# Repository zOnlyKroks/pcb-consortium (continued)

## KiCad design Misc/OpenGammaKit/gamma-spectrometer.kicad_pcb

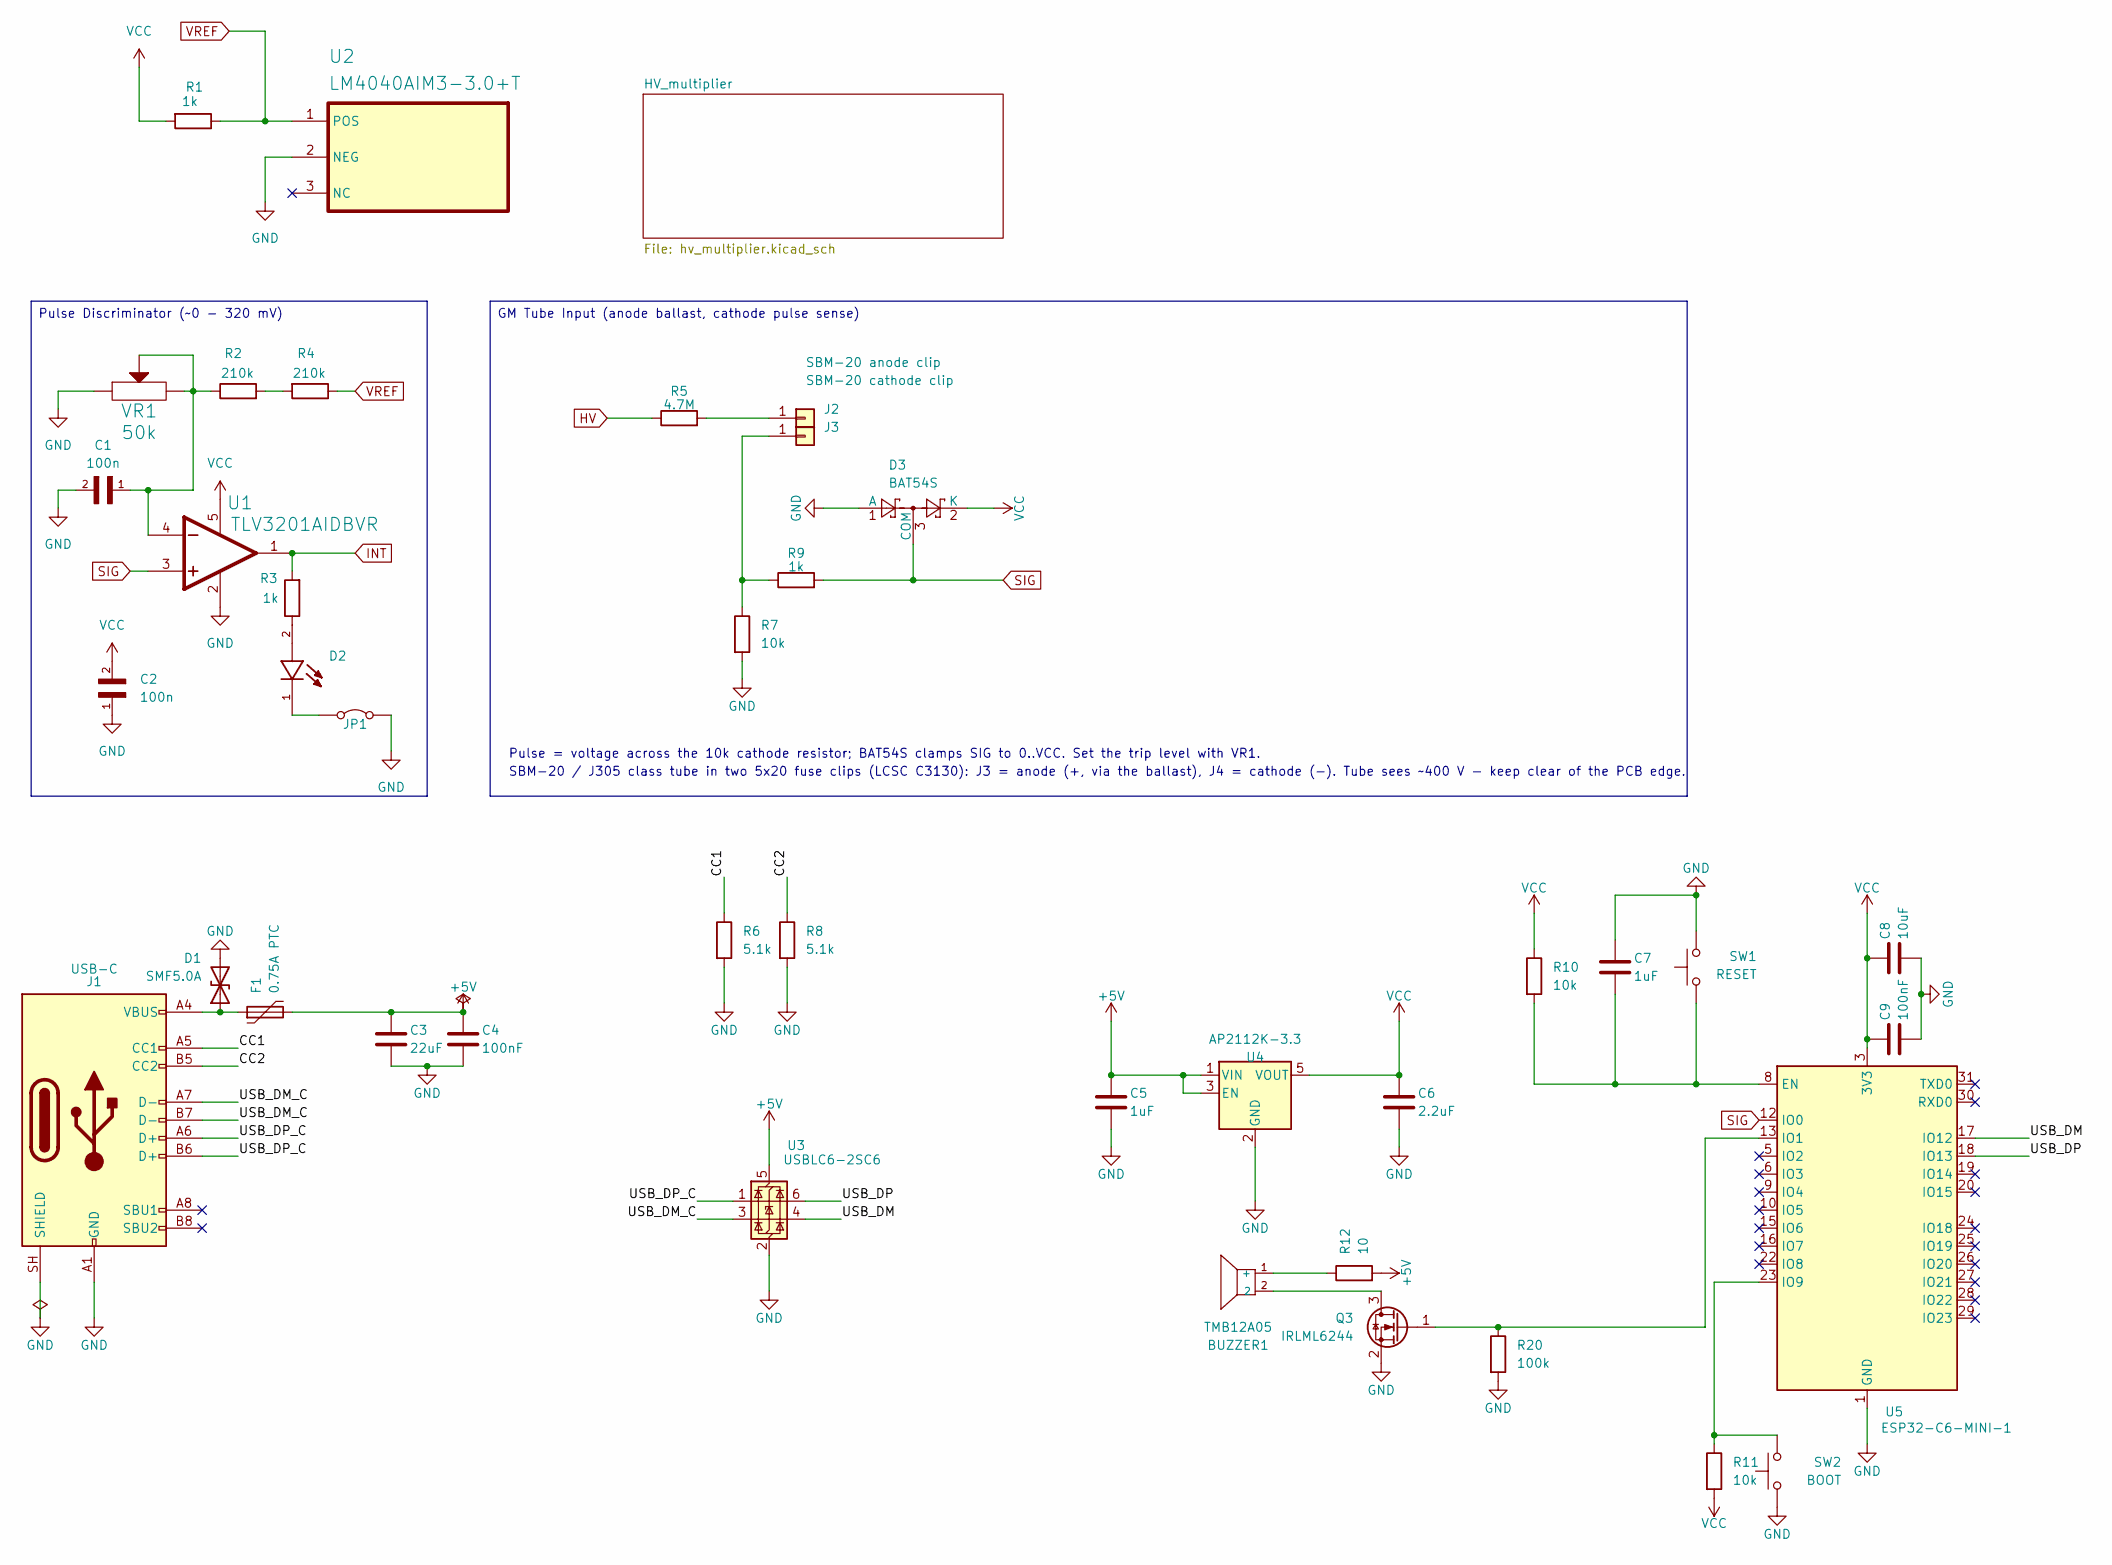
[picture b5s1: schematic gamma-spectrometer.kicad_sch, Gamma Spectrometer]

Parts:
BUZZER1: TMB12A05; C96093_BUZ-TH_BD12_0-P7_60-D0_6-FD; LCSC C96093
C1, C2: 100n; C_0603_1608Metric; PARTREV NA
C3: 22uF; C_1206_3216Metric
C4, C9: 100nF; C_0603_1608Metric
C5, C7: 1uF; C_0603_1608Metric
C6: 2.2uF; C_0603_1608Metric
C8: 10uF; C_0805_2012Metric
D1: SMF5.0A; D_SOD-123; LCSC C193402
D2: LTST-C190KGKT; LED_0603_1608Metric; LCSC C125094
D3: BAT54S; SOT-23; LCSC C458984
F1: 0.75A PTC; Fuse_1206_3216Metric; LCSC C47002356
J1: USB-C; USB_C_Receptacle_HRO_TYPE-C-31-M-12; LCSC C165948
J2: SBM-20 anode clip; FUSE-TH_5X20RHOSFUSECLIP-SEAT; LCSC C3130
J3: SBM-20 cathode clip; FUSE-TH_5X20RHOSFUSECLIP-SEAT; LCSC C3130
JP1: SolderJumper-2_P1.3mm_Open_TrianglePad1.0x1.5mm
Q3: IRLML6244; SOT-23; LCSC C143946
R1, R3, R9: 1k; R_0603_1608Metric
R2, R4: 210k; R_0603_1608Metric
R5: 4.7M; R_0603_1608Metric
R6, R8: 5.1k; R_0603_1608Metric
R7, R10, R11: 10k; R_0603_1608Metric
R12: 10; R_0603_1608Metric
R20: 100k; R_0603_1608Metric
SW1: RESET; SW_TS-1187A-B-A-B_2pin; LCSC C318884
SW2: BOOT; SW_TS-1187A-B-A-B_2pin; LCSC C318884
U1: TLV3201AIDBVR; SOT-23-5; LCSC C105188
U2: LM4040AIM3-3.0+T; SOT-23; LCSC C143326
U3: USBLC6-2SC6; SOT-23-6; LCSC C7519
U4: AP2112K-3.3; SOT-23-5; MPN AP2112K-3.3TRG1; LCSC C51118
U5: ESP32-C6-MINI-1; MPN ESP32-C6-MINI-1-N4; LCSC C5736265
VR1: 50k; Potentiometer_Bourns_3266W_Vertical

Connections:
+5V: C3.1, C4.1, C5.1, F1.2, R12.2, U3.5 (VBUS), U4.1 (VIN), U4.3 (EN); also elsewhere on the board
/CC1: J1.A5 (CC1), R6.1
/CC2: J1.B5 (CC2), R8.1
/USB_DM: U3.4 (I/O2), U5.17 (IO12)
/USB_DM_C: J1.A7 (D-), J1.B7 (D-), U3.3 (I/O2)
/USB_DP: U3.6 (I/O1), U5.18 (IO13)
/USB_DP_C: J1.A6 (D+), J1.B6 (D+), U3.1 (I/O1)
GND: C1.2, C2.1, C3.2, C4.2, C5.2, C6.2, C7.1, C8.2, C9.2, D1.2 (A2), D3.1 (A), J1.A1 (GND), J1.A12 (GND), J1.B1 (GND), J1.B12 (GND), J1.SH (SHIELD), JP1.2 (B), Q3.2 (S), R6.2, R7.2, R8.2, R20.2, SW1.2, SW2.1, U1.2 (GND), U2.2 (NEG), U3.2 (GND), U4.2 (GND), U5.1 (GND), U5.2 (GND), U5.11 (GND), U5.14 (GND), U5.36 (GND), U5.37 (GND), U5.38 (GND), U5.39 (GND), U5.40 (GND), U5.41 (GND), U5.42 (GND), U5.43 (GND), U5.44 (GND), U5.45 (GND), U5.46 (GND), U5.47 (GND), U5.48 (GND), U5.49 (GND), U5.50 (GND), U5.51 (GND), U5.52 (GND), U5.53 (GND), VR1.1 (CCW); also elsewhere on the board
HV: R5.1; also elsewhere on the board
INT: R3.2, U1.1 (OUT)
unnamed: BUZZER1.1 (+), R12.1
unnamed: D1.1 (A1), F1.1, J1.A4 (VBUS), J1.A9 (VBUS), J1.B4 (VBUS), J1.B9 (VBUS)
unnamed: D2.2, R3.1
unnamed: J2.1 (Pin_1_1), R5.2
unnamed: J3.1 (Pin_1_1), R7.1, R9.1
unnamed: D2.1, JP1.1 (A)
unnamed: BUZZER1.2, Q3.3 (D)
unnamed: Q3.1 (G), R20.1, U5.13 (IO1)
unnamed: R2.2, R4.2
unnamed: C1.1, R2.1, U1.4 (IN-), VR1.2 (WIPER), VR1.3 (CW)
unnamed: C7.2, R10.2, SW1.1, U5.8 (EN)
unnamed: R11.1, SW2.2, U5.23 (IO9)
SIG: D3.3 (COM), R9.2, U1.3 (IN+), U5.12 (IO0)
VCC: C2.2, C6.1, C8.1, C9.1, D3.2 (K), R1.2, R10.1, R11.2, U1.5 (VCC), U4.5 (VOUT), U5.3 (3V3); also elsewhere on the board
VREF: R1.1, R4.1, U2.1 (POS); also elsewhere on the board

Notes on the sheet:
SBM-20 / J305 class tube in two 5x20 fuse clips (LCSC C3130): J3 = anode (+, via the ballast), J4 = cathode (-). Tube sees ~400 V - keep clear of the PCB edge.
Pulse = voltage across the 10k cathode resistor; BAT54S clamps SIG to 0..VCC. Set the trip level with VR1.
Pulse Discriminator (~0 - 320 mV)
GM Tube Input (anode ballast, cathode pulse sense)

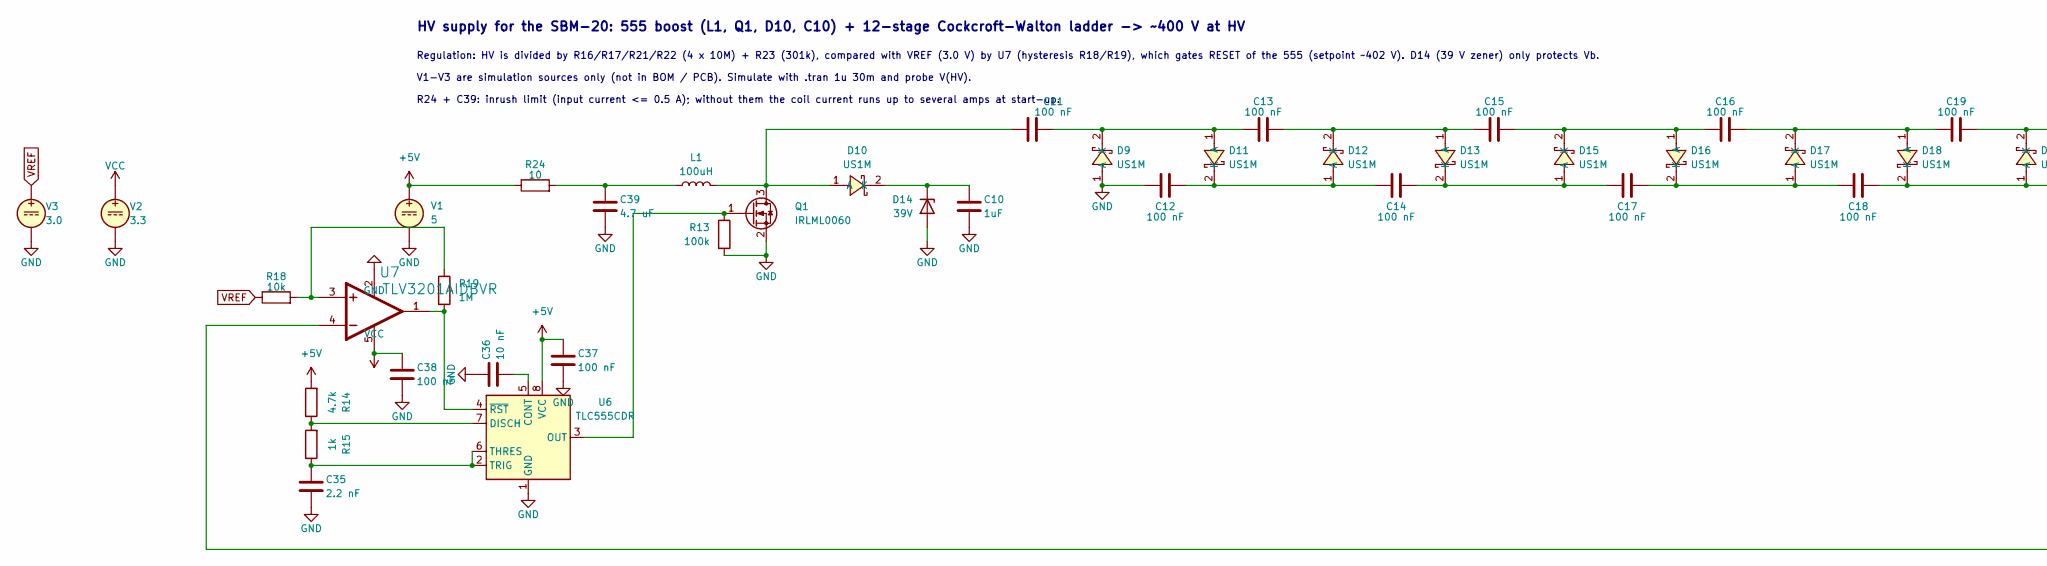
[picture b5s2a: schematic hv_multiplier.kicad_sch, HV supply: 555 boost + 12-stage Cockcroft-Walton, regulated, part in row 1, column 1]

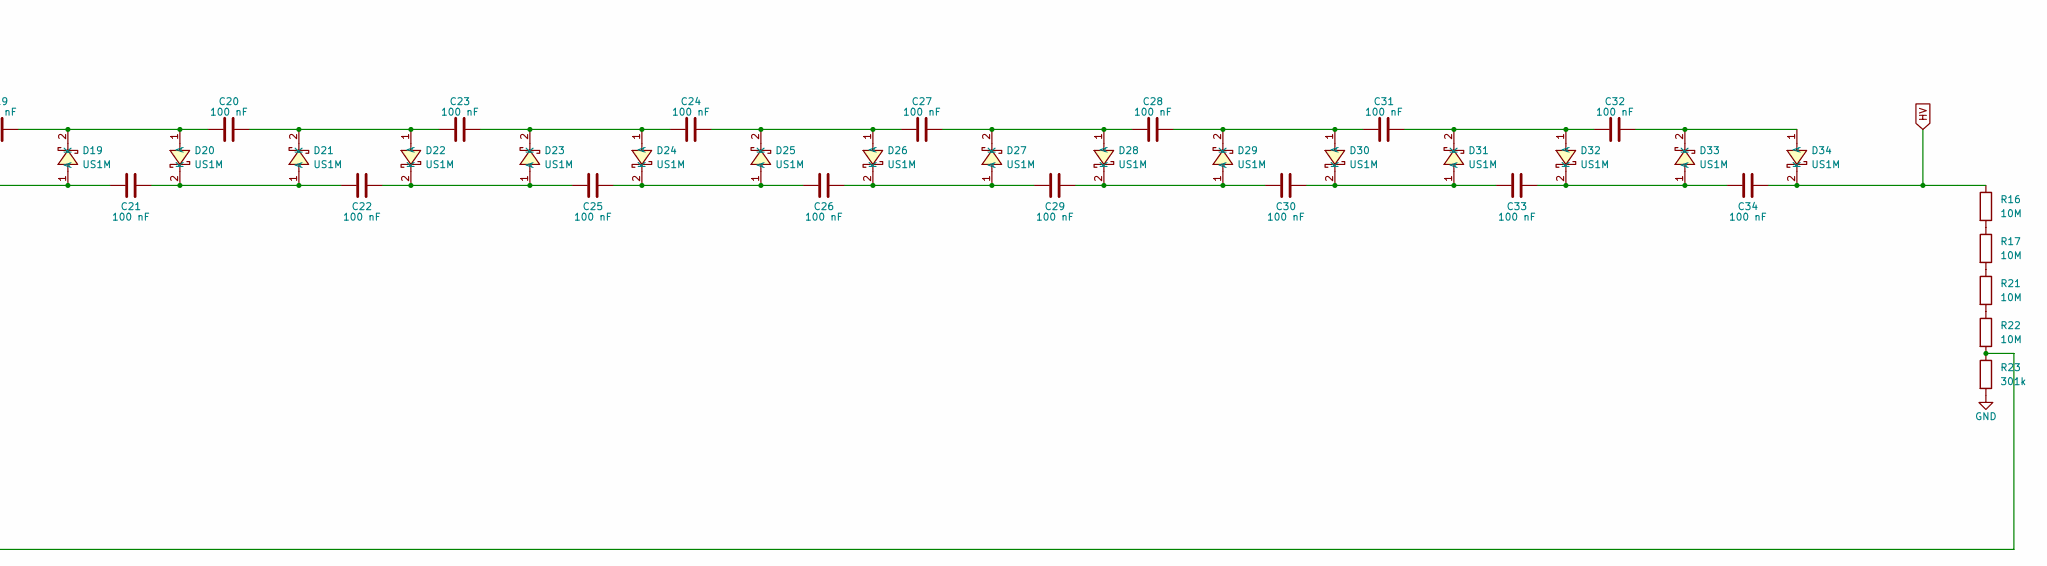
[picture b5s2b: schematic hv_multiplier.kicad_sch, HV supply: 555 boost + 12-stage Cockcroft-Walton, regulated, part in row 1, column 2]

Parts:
C10: 1uF; C_1206_3216Metric; LCSC C13832
C11, C12, C13, C14, C15, C16, C17, C18, C19, C20, C21, C22, C23, C24, C25, C26, C27, C28, C29, C30, C31, C32, C33, C34: 100 nF; C_0805_2012Metric; LCSC C28233
C35: 2.2 nF; C_0603_1608Metric
C36: 10 nF; C_0603_1608Metric
C37, C38: 100 nF; C_0603_1608Metric
C39: 4.7 uF; C_0805_2012Metric; LCSC C1746
D9, D10, D11, D12, D13, D15, D16, D17, D18, D19, D20, D21, D22, D23, D24, D25, D26, D27, D28, D29, D30, D31, D32, D33, D34: US1M; C7420317_SMA_L4.3-W2.6-LS5.0-FD; LCSC C7420317
D14: 39V; D_SOD-123; LCSC C353532
L1: 100uH; C280633_IND-SMD_L10.5-W10.5; LCSC C280633
Q1: IRLML0060; SOT-23; LCSC C67274
R13: 100k; R_0603_1608Metric
R14: 4.7k; R_0603_1608Metric
R15: 1k; R_0603_1608Metric
R16, R17, R21, R22: 10M; R_0805_2012Metric; LCSC C325949
R18: 10k; R_0603_1608Metric
R19: 1M; R_0603_1608Metric
R23: 301k; R_0603_1608Metric
R24: 10; R_2512_6332Metric; LCSC C171290
U6: TLC555CDR; SOIC-8_3.9x4.9mm_P1.27mm; LCSC C6986
U7: TLV3201AIDBVR; SOT-23-5; LCSC C105188
V1: 5
V2: 3.3
V3: 3.0

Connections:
+5V: C37.1, R14.2, R24.1, U6.8 (VCC), V1.1; also elsewhere on the board
GND: C10.2, C12.1, C35.2, C36.1, C37.2, C38.2, C39.2, D9.1 (A), D14.2 (A), Q1.2 (S), R13.2, R23.2, U6.1 (GND), U7.2 (GND), V1.2, V2.2, V3.2; also elsewhere on the board
HV: C34.2, D34.2 (K), R16.1; also elsewhere on the board
unnamed: C39.1, L1.1, R24.2
unnamed: C11.1, D10.1 (A), L1.2, Q1.3 (D)
unnamed: C10.1, D10.2 (K), D14.1 (K)
unnamed: C11.2, C13.1, D9.2 (K), D11.1 (A)
unnamed: C12.2, C14.1, D11.2 (K), D12.1 (A)
unnamed: C13.2, C15.1, D12.2 (K), D13.1 (A)
unnamed: C14.2, C17.1, D13.2 (K), D15.1 (A)
unnamed: C15.2, C16.1, D15.2 (K), D16.1 (A)
unnamed: C17.2, C18.1, D16.2 (K), D17.1 (A)
unnamed: C16.2, C19.1, D17.2 (K), D18.1 (A)
unnamed: C18.2, C21.1, D18.2 (K), D19.1 (A)
unnamed: C19.2, C20.1, D19.2 (K), D20.1 (A)
unnamed: C21.2, C22.1, D20.2 (K), D21.1 (A)
unnamed: C20.2, C23.1, D21.2 (K), D22.1 (A)
unnamed: C22.2, C25.1, D22.2 (K), D23.1 (A)
unnamed: C23.2, C24.1, D23.2 (K), D24.1 (A)
unnamed: C25.2, C26.1, D24.2 (K), D25.1 (A)
unnamed: C24.2, C27.1, D25.2 (K), D26.1 (A)
unnamed: C26.2, C29.1, D26.2 (K), D27.1 (A)
unnamed: C27.2, C28.1, D27.2 (K), D28.1 (A)
unnamed: C29.2, C30.1, D28.2 (K), D29.1 (A)
unnamed: C28.2, C31.1, D29.2 (K), D30.1 (A)
unnamed: C30.2, C33.1, D30.2 (K), D31.1 (A)
unnamed: C31.2, C32.1, D31.2 (K), D32.1 (A)
unnamed: C33.2, C34.1, D32.2 (K), D33.1 (A)
unnamed: C32.2, D33.2 (K), D34.1 (A)
unnamed: Q1.1 (G), R13.1, U6.3 (OUT)
unnamed: R16.2, R17.1
unnamed: R17.2, R21.1
unnamed: R21.2, R22.1
unnamed: C36.2, U6.5 (CONT)
unnamed: R14.1, R15.2, U6.7 (DISCH)
unnamed: C35.1, R15.1, U6.2 (TRIG), U6.6 (THRES)
unnamed: R19.2, U6.4 (~RST), U7.1 (OUT)
unnamed: R18.2, R19.1, U7.3 (IN+)
unnamed: R22.2, R23.1, U7.4 (IN-)
VCC: C38.1, U7.5 (VCC), V2.1; also elsewhere on the board
VREF: R18.1, V3.1; also elsewhere on the board

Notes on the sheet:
Regulation: HV is divided by R16/R17/R21/R22 (4 x 10M) + R23 (301k), compared with VREF (3.0 V) by U7 (hysteresis R18/R19), which gates RESET of the 555 (setpoint ~402 V). D14 (39 V zener) only protects Vb.
V1-V3 are simulation sources only (not in BOM / PCB). Simulate with .tran 1u 30m and probe V(HV).
HV supply for the SBM-20: 555 boost (L1, Q1, D10, C10) + 12-stage Cockcroft-Walton ladder -> ~400 V at HV
R24 + C39: inrush limit (input current <= 0.5 A); without them the coil current runs up to several amps at start-up.

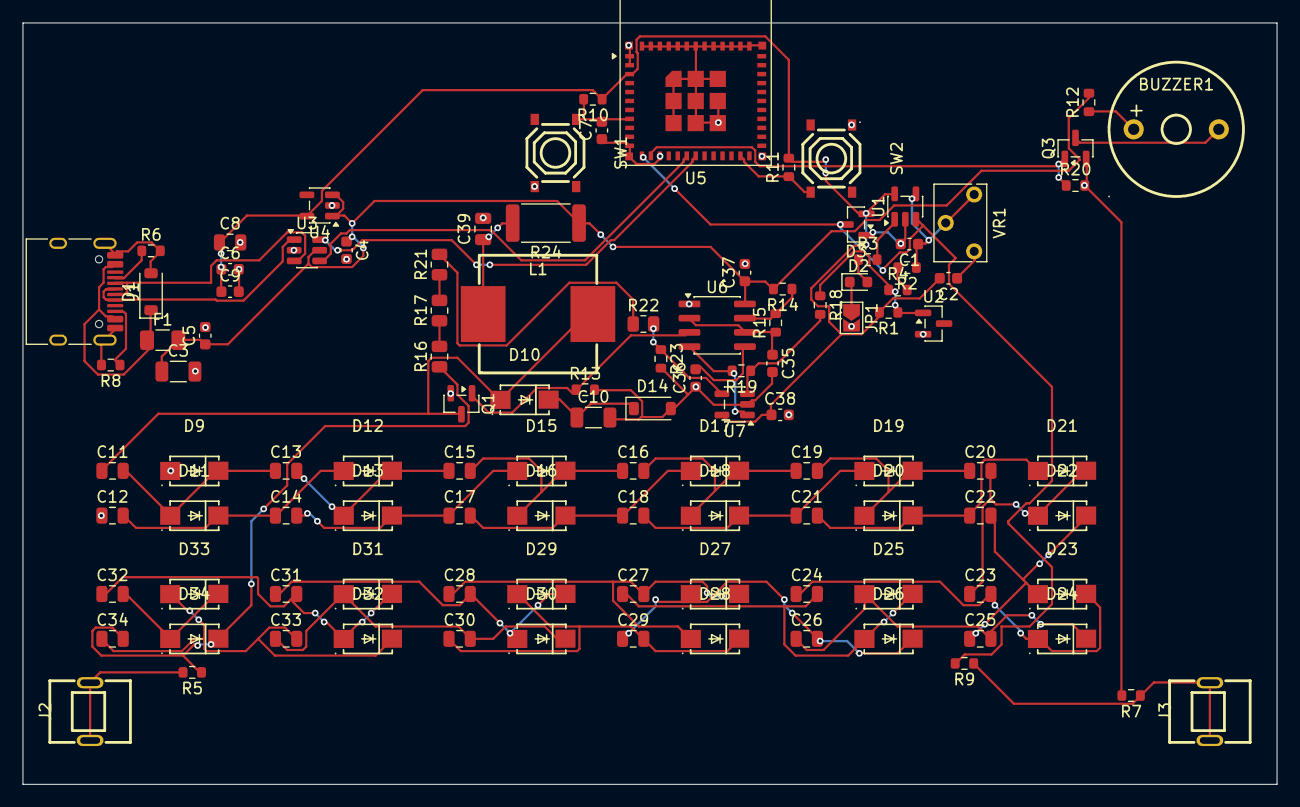
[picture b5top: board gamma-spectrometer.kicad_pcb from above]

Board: 2 copper layers, 112.0 x 68.0 mm, 111 parts (0 on the bottom side), 61 nets.

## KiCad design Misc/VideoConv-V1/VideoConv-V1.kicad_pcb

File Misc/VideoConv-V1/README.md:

# VideoConv-V1: analog video to HDMI + VGA converter

"Works with whatever you throw at it": SCART (RGB, composite, S-Video), component YPbPr up to 1080p, composite.
Hand-solderable (no BGA). **Schematic only**: no PCB, no simulation, and the FPGA gateware is a specification, not code.

```
SCART  ---R,G,B--------------------------------------+
RCA Y/Pb/Pr --75R-0.1u-----------------------------> TVP7002 --24-bit RGB/YCbCr + sync + pixel clock--+
SCART pin 20 / RCA CVBS --attenuate-> TVP5150 --BT.656 8-bit + 27 MHz--------------------------------+--> iCE40HX4K
SCART pin 15 (S-Video C) ------------^                                                               |  line-double / bob-deinterlace /
SCART pin 16, pin 8 --comparators--------------------------------------------------------------------+  YCbCr->RGB / HD pass-through
                                                  I2C <------------------------------------------------+
                                                                  24-bit RGB + DE/HS/VS/clk -> TFP410 -> TPD12S016 -> HDMI (DVI video)
                                                                  6-bit R-2R DACs x3 + HS/VS -> DE-15 VGA
```
All analog inputs go through ESD clamps (USBLC6-4SC6, or a bidirectional TVS on the audio pair) at the connector.

## Schematic structure (hierarchical)
`VideoConv-V1.kicad_sch` is the root: one sheet symbol per block, with sheet pins and net labels for every signal that crosses
between blocks. The blocks live in `sheets/`:

| sheet | content |
|---|---|
| `Power` | USB-C 5 V, TVS + PTC, 3.3 V and 1.9 V bucks, 1.8 V and 1.2 V LDOs, ferrite-filtered analog rails, power flags |
| `Inputs` | SCART + RCA jacks, 75 ohm terminations, ESD arrays, TVP5150 attenuators + CVBS jumper, SCART pin 16 / 8 comparators, audio out |
| `TVP7002` | the digitiser, 22 ohm output arrays, PLL filter, unused-input terminations, decoupling |
| `TVP5150` | the decoder, 14.31818 MHz crystal, reference caps, strap resistors |
| `FPGA` | iCE40HX4K (5 symbol units: 4 I/O banks + power/config), 27 MHz oscillator, SPI flash, programming header, MODE button, LEDs, I2C pull-ups |
| `HDMI` | TFP410 with its strap network, TPD12S016, HDMI connector |
| `VGA` | three 6-bit R-2R ladders, sync resistors, DE-15 |

Supply rails (`+3V3`, `+1V9A`, ...) are global power symbols and need no sheet pins. The generator (`tools/gen_sch.py`, assembled from
the layout engine + `hier_part.py` + `design_part.py`) routes every part to the sheet selected with `sh.S("Name")`; any net
label used on more than one sheet automatically becomes a hierarchical label there and a sheet pin + label on the root.

## Why this architecture
The converter has to cope with 15 kHz sources (240p consoles, 480i/576i), 31 kHz (480p), HD component, sync-on-green,
composite sync and VCR-grade CVBS. No single chip does that and also produces a modern output, so:

| block | part | job |
|---|---|---|
| analog front end 1 | TVP7002 (TI, 100-pin HTQFP) | 3x 10-bit 165 MSPS ADC, 3 inputs per colour, 3 sync-on-green slicers, H-PLL: SCART RGB + component, SD to 1080p |
| analog front end 2 | TVP5150AM1 (TI, 32-pin TQFP) | NTSC/PAL/SECAM decoder, 4-line comb filter, CVBS or S-Video, BT.656 out |
| processing | iCE40HX4K-TQ144 | line buffers in BRAM (line-doubling, bob-deinterlace), colour-space conversion, HD pass-through, I2C master for the two chips, SCART sensing |
| output 1 | TFP410 + TPD12S016 | 24-bit RGB -> TMDS (DVI video, accepted by HDMI sinks); TPD12S016 = ESD, DDC / hot-plug level shifting, current-limited 5 V |
| output 2 | 12 resistors per channel | 6-bit R-2R DACs into 75 ohm, HS/VS direct (VGA monitors and capture cards) |

The FPGA configures both decoders over I2C (no separate MCU): a small sequencer replays one register table per input
mode, selected with the MODE button or from the SCART signals. TFP410 is pin-strapped and needs no I2C.

## Inputs and how they map
| connector | signal | goes to |
|---|---|---|
| SCART pins 15 / 11 / 7 | R, G, B (0.7 Vpp) | TVP7002 RIN_1 / GIN_1 / BIN_1, 75 ohm + 0.1 uF each |
| SCART pin 20 | CVBS or composite sync | TVP7002 SOGIN_1 (1 nF) and TVP5150 AIP1A through the attenuator (jumper position "B") |
| SCART pin 15 | S-Video chroma | TVP5150 AIP1B (same node as red) |
| SCART pin 16 | fast blanking (RGB active) | 75 ohm load -> comparator -> FPGA `SC_RGB` (high when above 0.7 V) |
| SCART pin 8 | function switch (aspect / AV) | /4.3 divider -> two comparators -> FPGA `SC_FS1` (above 3 V) and `SC_FS2` (above 8 V) |
| RCA Y, Pb, Pr | component (SoG on Y) | TVP7002 GIN_2 / BIN_2 / RIN_2, SOGIN_2 |
| RCA CVBS | composite | TVP5150 AIP1A (jumper position "A") |
| SCART pins 2 / 6 | audio | 3.5 mm line out (analog pass-through, no HDMI audio) |

Pin 8 states per SCART: 0 to 2 V = none / TV, 4.5 to 7 V = 16:9, 9.5 to 12 V = 4:3 (SC_FS1 high only = 16:9, both high = 4:3).
Auto-select rule for the gateware: SC_RGB high -> SCART RGB path, otherwise composite / S-Video; the button overrides.
Comparators are an LM339 on 5 V with 3.3 V threshold dividers (0.71 V and 1.87 V after the /4.3 divider) and 10 k pull-ups to 3.3 V.

Unused TVP7002 inputs (RIN_3/GIN_3/GIN_4/BIN_3, SOGIN_3) and its HSYNC/VSYNC/CLAMP/COAST/TMS/PWDN pins are terminated as
the datasheet says. A PC VGA input is not included.

## Input protection
- 12 signal lines through three USBLC6-4SC6 (SOT-23-6, 4 channels each, clamp to +5 V and GND, about 3.5 pF), one per
  group: SCART RGB + CVBS, component + RCA CVBS, pin 16 + the pin 8 divider node. Pin 8 itself (up to 12 V) is protected
  by the 33 k series resistor, so the clamp sits on the divided node.
- SCART audio is bipolar, so it gets bidirectional TVS diodes (SMF5.0CA) instead of the clamp arrays.
- HDMI side: TPD12S016 gives 15 kV ESD on TMDS / DDC / HPD / CEC and 5 V current limiting.
- Note: the clamp arrays reference the board's 5 V rail; with the board unpowered, a source driving the inputs only
  leaks a little current into that rail.

## HD inputs (720p / 1080i / 1080p)
Hardware: TVP7002 samples up to 165 MSPS (sync-on-green tri-level sync handled by its slicers), DATACLK goes to an FPGA
global clock pin, TFP410 accepts 25 to 165 MHz, and the FPGA can generate or pass 74.25 / 148.5 MHz. `gateware/tvp7002_modes.csv`
lists the H-PLL settings (PLLDIV, VCO range, charge-pump current) for 480i/p, 576i/p, 720p, 1080i and 1080p, taken from
datasheet Table 4 (the register pairs were checked: reg 01h/02h encode the PLLDIV total for every row).

Gateware specification for HD:
1. Mode detect: read the TVP7002 line/frame status (or measure HS/VS in the FPGA) and pick a row of the table; HD mode =
   pixel clock >= 74.25 MHz.
2. HD data path = **pass-through**: TVP7002 DATACLK is the system clock, data goes through a few register stages, DE is made
   from the HS/VS pulses and the active-video counters (TVP7002 can also output a data-enable on FIDOUT via register 17h),
   output clock IDCK = DATACLK delayed by one stage. No scaling: the sink must accept 720p / 1080i / 1080p (all HDMI TVs do).
3. Component 4:2:2 / YCbCr -> RGB with BT.709 for HD (BT.601 for SD); TVP7002 can also do the colour-space conversion itself
   (its CSC block defaults to the HDTV coefficients).
4. 1080i from a console is passed as interlaced (no deinterlacing in v1).
5. VGA out on HD: the 6-bit R-2R stage runs at 74 MHz with about 75 ohm source impedance, so expect softer edges than HDMI;
   use HDMI for HD.

SD path as before: TVP7002 oversamples 15 kHz sources at 27 MHz (PLLDIV 1716 / 1728, see the CSV), the FPGA keeps every
second pixel in, reads at 27 MHz, and doubles lines (240p -> 480p) or bob-deinterlaces (480i -> 480p). Output clock = input
sample clock, locked, no frame buffer.

## Numbers I took from the datasheets (all in `datasheets/`)
- **TVP7002**: 1.9 V analog/digital core (1.8 to 2.0 V), 3.3 V analog and I/O; inputs AC coupled with 0.1 uF; SOG coupled
  with 1 nF; PLL loop filter = 1.5 k + 0.1 uF on FILT1 and 4.7 nF on FILT2 to PLL_F; I2C 0xB8 with I2CA low (2.2 k);
  27 MHz external reference; 8 MSBs of each colour through 22 ohm.
- **TVP5150AM1**: 1.8 V core/analog (ferrite-filtered analog rail), 3.3 V I/O; maximum input 0.75 Vpp, so CVBS goes through
  24.9 + 49.9 ohm (75 ohm termination, x0.67) with an 820 pF anti-alias cap; 14.31818 MHz crystal, 27 pF loads, 100 k parallel;
  REFP / REFM 1 uF; I2CSEL high = 0xBA; INTREQ pin pulled down.
- **TFP410** (pin-strap): VREF = DVDD, BSEL high (24-bit single edge), EDGE high (rising), ISEL / DSEL / DKEN / CTL / RESERVED low,
  PD high, TFADJ 510 ohm 1 % to TVDD, IDCK- low. D23..16 red, D15..8 green, D7..0 blue.
- **TPD12S016PW** (source-port part, replaces the TPD12S520 of the first version): TMDS pins connect directly to controller and
  connector; VCCA = 3.3 V, VCC5V = 5 V, 5V_OUT -> HDMI pin 18 (current-limited); CT_HPD pulled high enables the part, HPD_A drives
  both the FPGA and LS_OE (datasheet Fig. 15, "one control line" mode); SCL_A/SDA_A to the FPGA (internal pull-ups on both
  sides, none added); CEC_B to the connector, CEC_A open. The order of the 8 TMDS pins within their group is only a routing
  convenience (inferred from the pin-function table).
- **AP62300** bucks (TSOT-23-6 pinout 1 GND, 2 SW, 3 VIN, 4 FB, 5 EN, 6 BST): 3.3 V (R1 31.6 k, R2 10 k, L 3.3 uH, 10 uF in, 2x22 uF out)
  and 1.9 V (R1 13.7 k, L 2.2 uH) from 5 V. Rails: 5 V (USB-C) -> 3.3 V, 1.9 V, 1.8 V LDO, 1.2 V LDO; ferrite-filtered analog copies.

## FPGA
iCE40HX4K-TQ144, 99 constrained pins (`gateware/pins.pcf`, generated from the schematic): bank 3 = TVP7002 data (pixel clock on a
global-buffer pin), bank 2 = TVP5150 BT.656 + I2C + UI, bank 0 = TFP410 data, bank 1 = VGA DAC bits, TFP410 VSYNC, 27 MHz clock,
HPD, DDC, SCART sense. All banks 3.3 V. Config: W25Q32JV SPI flash, a 7-pin programming header (hold CRESET low to program
externally), CDONE LED. Remaining gateware work: I2C sequencer + register ROM per mode, BT.656 decoder, line buffer
(line-double / bob), HD pass-through, timing generators, test pattern, SCART auto-select. Nothing of this is written yet.

## Verification done
- Generated with `tools/gen_sch.py` (= engine + `design_part.py`, symbols from `gen_symbols.py`); ERC: **0 errors**, 4 warnings
  (all intentional: I/O pins tied to GND on a net carrying the GND power flag, and the GND alias labels `TV_UNUSED` / `FPGA_GND0` / `TF_LO`).
- `tools/check_nets.py` exports the (hierarchical) netlist with kicad-cli and compares **all 882 intended pin connections** with KiCad's nets:
  0 mismatches across the sheet boundaries, no merged nets (this found and fixed a real GND-to-3.3 V short during layout).
- TVP7002 symbol checked against the datasheet pin diagram (97 of 100 entries by script, the other 3 by hand); TVP5150 spot-checked;
  TPD12S016 from the pin-function table; AP62300 pinout checked per package column.
- Footprints exist in KiCad stock except the SCART and RCA jacks.

## Not done / open points
1. **No PCB.** Analog video wants a 4-layer board with a solid ground plane; put the USBLC6 arrays and TPD12S016 right at their connectors;
   the TVP7002 exposed pad footprint (TQFP-100 EP 5x5 here) must be checked against TI's PZP drawing.
2. **No gateware, no simulation.** Nothing here has been powered up.
3. SCART / RCA jack footprints and part numbers. LCSC numbers are in the schematic (property `LCSC Part #`) and in `bom.csv`; J6 (SCART), J7 (3.5 mm jack), SW1 (C&K RS282G05A3) have no LCSC equivalent, L1/L2/FB1-6 are LCSC substitutes (see `tools/add_lcsc.py`).
4. HDMI is video only (no audio, no InfoFrames), CEC is only passed to the connector. Audio is the SCART/analog line out.
5. 1080i / 1080p out of the box is pass-through only (no scaling), VGA out at HD is marginal (see above).
6. SCART pin 8 / 16 sensing uses fixed thresholds (no hysteresis); a noisy console may need a 100 nF on the comparator inputs.
7. TVP7002 is rated 0 to 70 C. Inductors / ferrites / crystal: values from datasheets, parts not chosen (inductors Isat >= 4 A, shielded).
8. The TPD12S016 TMDS pin order and the AP62300 pin numbering are taken from the datasheet text, not from a pin drawing I could view.

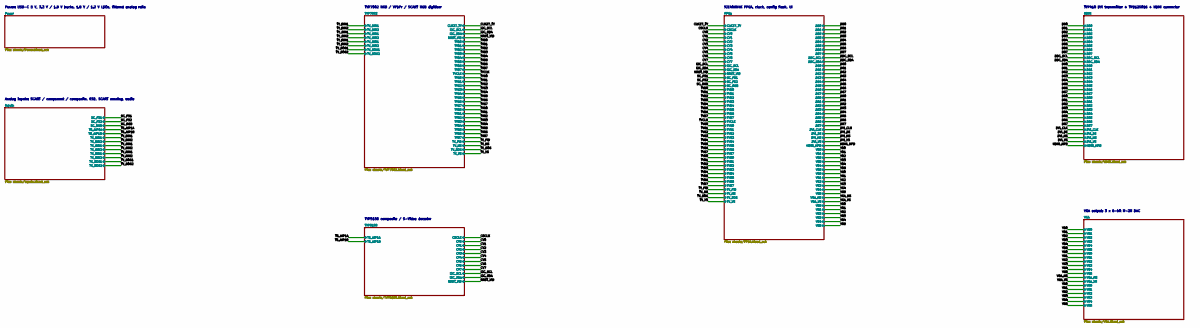
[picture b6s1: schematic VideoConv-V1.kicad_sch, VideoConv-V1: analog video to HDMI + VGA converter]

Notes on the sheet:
TFP410 DVI transmitter + TPD12S016 + HDMI connector
VGA output: 3 x 6-bit R-2R DAC
iCE40HX4K FPGA, clock, config flash, UI
Power: USB-C 5 V, 3.3 V / 1.9 V bucks, 1.8 V / 1.2 V LDOs, filtered analog rails
Analog inputs: SCART / component / composite, ESD, SCART sensing, audio
TVP5150 composite / S-Video decoder
TVP7002 RGB / YPbPr / SCART RGB digitiser

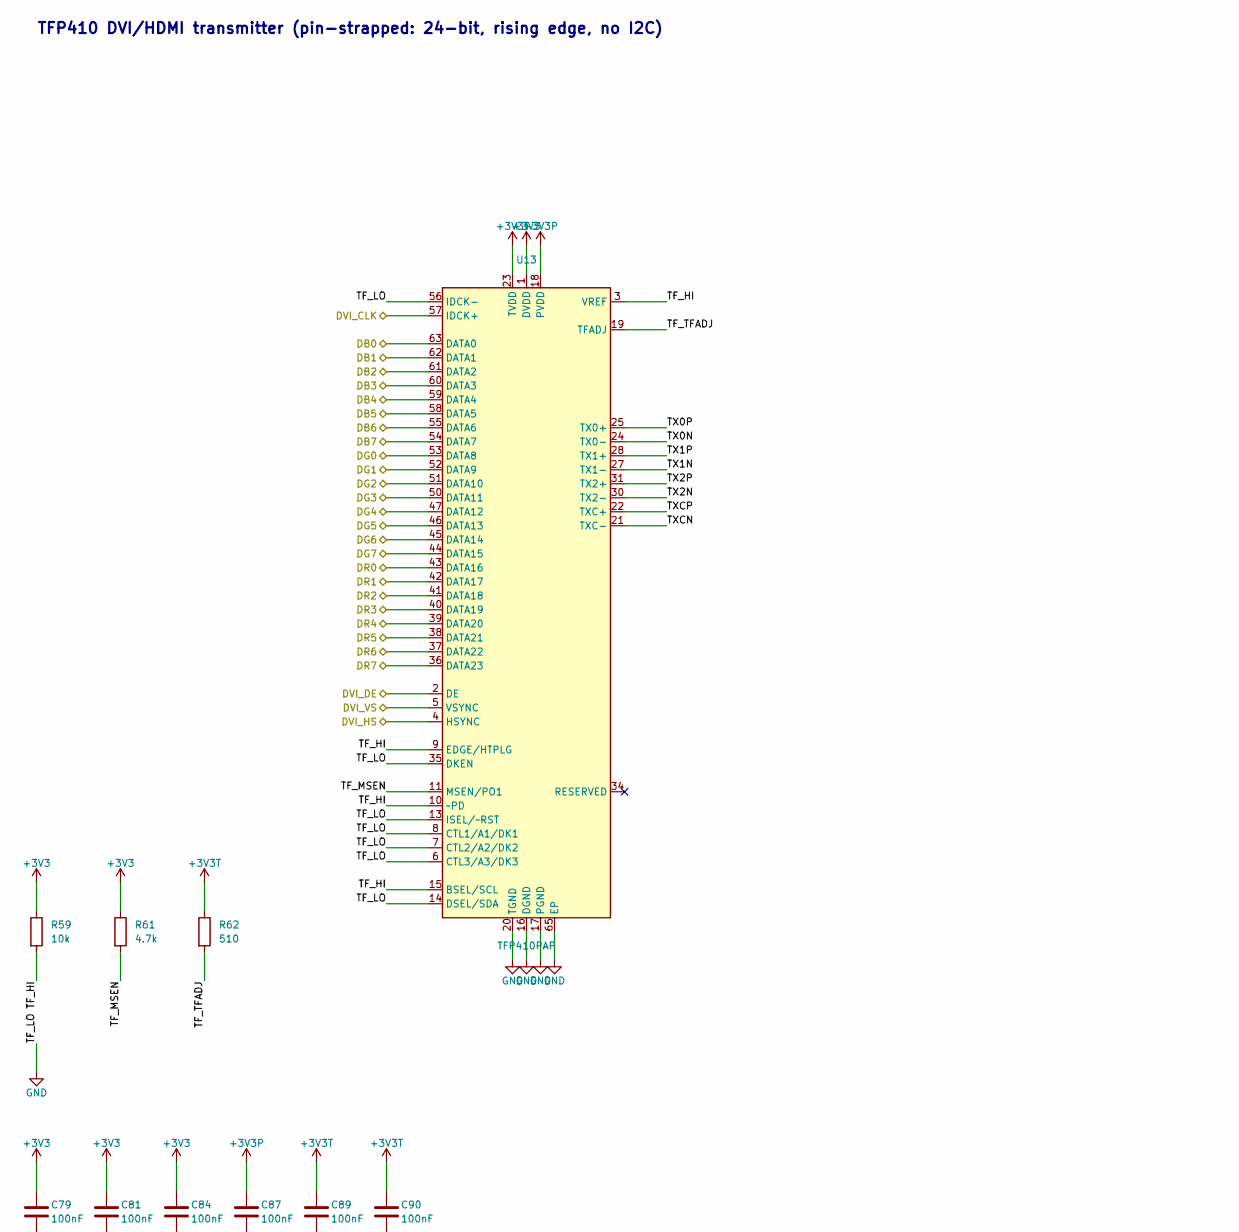
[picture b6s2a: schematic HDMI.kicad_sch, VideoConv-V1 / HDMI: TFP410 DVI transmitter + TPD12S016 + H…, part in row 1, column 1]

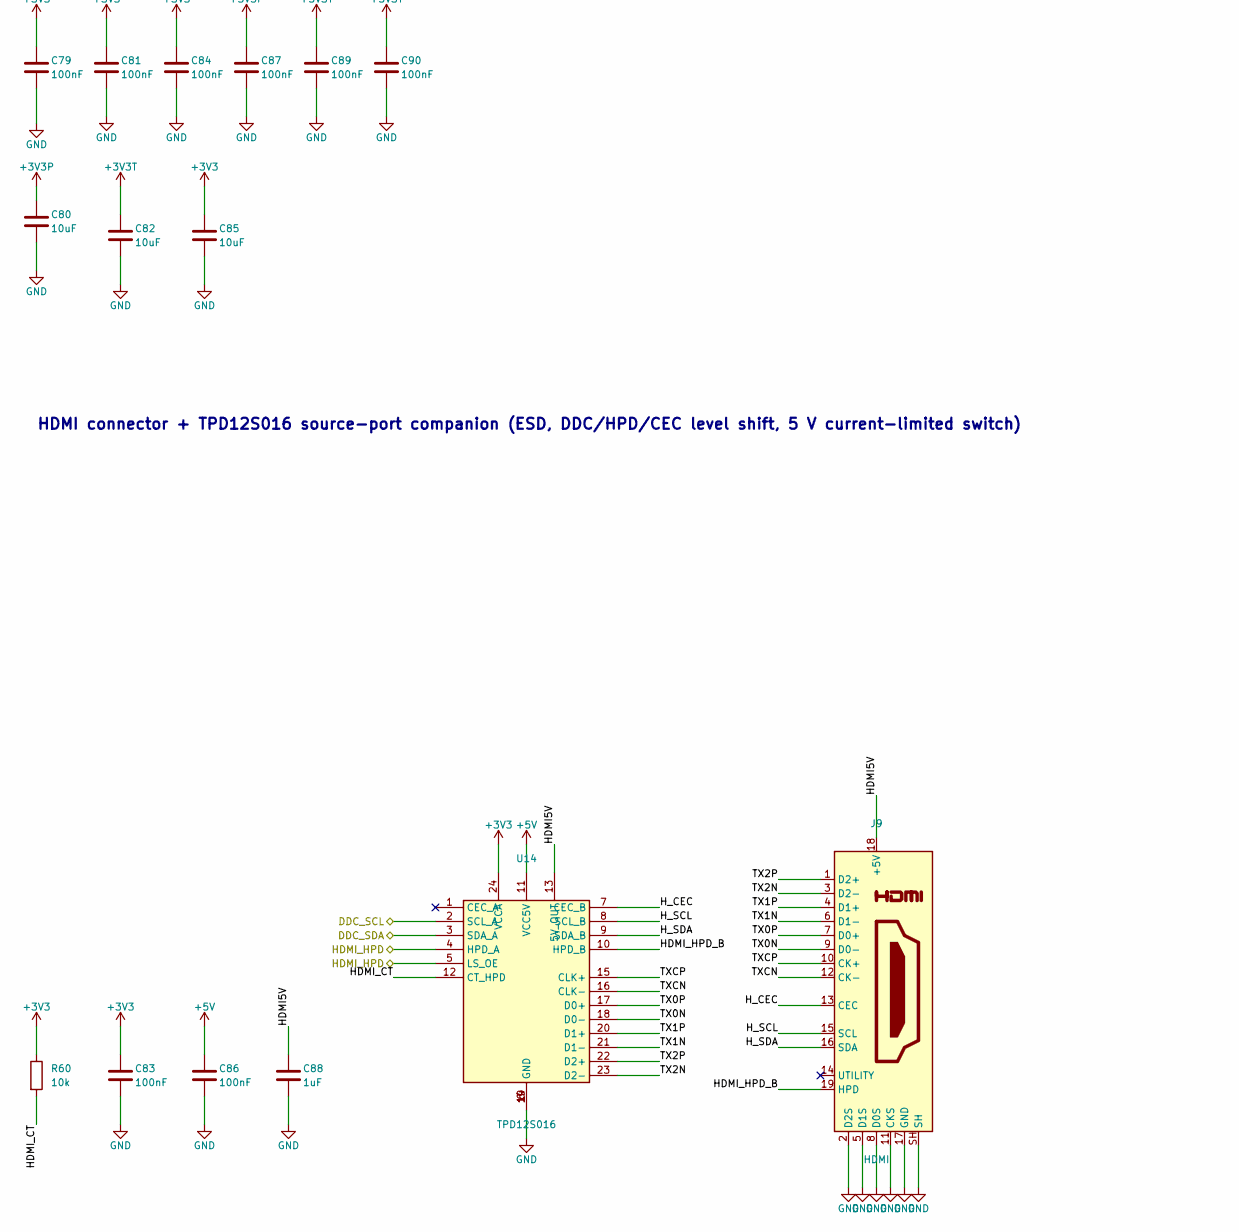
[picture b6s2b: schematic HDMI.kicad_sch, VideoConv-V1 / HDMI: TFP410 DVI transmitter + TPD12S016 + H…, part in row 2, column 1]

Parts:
C79, C81, C83, C84, C86, C87, C89, C90: 100nF; C_0603_1608Metric; LCSC Part # C1591
C80, C82, C85: 10uF; C_0805_2012Metric; LCSC Part # C15850
C88: 1uF; C_0805_2012Metric; LCSC Part # C116352
J9: HDMI; HDMI_A_Molex_208658-1001_Horizontal; LCSC Part # C916313
R59, R60: 10k; R_0603_1608Metric; LCSC Part # C25804
R61: 4.7k; R_0603_1608Metric; LCSC Part # C23162
R62: 510; R_0603_1608Metric; Tolerance 1%; LCSC Part # C23193
U13: TFP410PAP; Texas_TQFP-64-1EP_10x10mm_P0.5mm_EP8x8mm_Mask5x5mm_ThermalV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; MPN TFP410PAPR; LCSC Part # C1543847
U14: TPD12S016; TSSOP-24_4.4x7.8mm_P0.65mm; MPN TPD12S016PWR; LCSC Part # C201665

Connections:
+3V3: C79.1, C81.1, C83.1, C84.1, C85.1, R59.1, R60.1, R61.1, U13.1 (DVDD), U13.12 (DVDD), U13.33 (DVDD), U14.24 (VCCA); also elsewhere on the board
+3V3P: C80.1, C87.1, U13.18 (PVDD); also elsewhere on the board
+3V3T: C82.1, C89.1, C90.1, R62.1, U13.23 (TVDD), U13.29 (TVDD); also elsewhere on the board
+5V: C86.1, U14.11 (VCC5V); also elsewhere on the board
/DB0: U13.63 (DATA0); also elsewhere on the board
/DB1: U13.62 (DATA1); also elsewhere on the board
/DB2: U13.61 (DATA2); also elsewhere on the board
/DB3: U13.60 (DATA3); also elsewhere on the board
/DB4: U13.59 (DATA4); also elsewhere on the board
/DB5: U13.58 (DATA5); also elsewhere on the board
/DB6: U13.55 (DATA6); also elsewhere on the board
/DB7: U13.54 (DATA7); also elsewhere on the board
/DDC_SCL: U14.2 (SCL_A); also elsewhere on the board
/DDC_SDA: U14.3 (SDA_A); also elsewhere on the board
/DG0: U13.53 (DATA8); also elsewhere on the board
/DG1: U13.52 (DATA9); also elsewhere on the board
/DG2: U13.51 (DATA10); also elsewhere on the board
/DG3: U13.50 (DATA11); also elsewhere on the board
/DG4: U13.47 (DATA12); also elsewhere on the board
/DG5: U13.46 (DATA13); also elsewhere on the board
/DG6: U13.45 (DATA14); also elsewhere on the board
/DG7: U13.44 (DATA15); also elsewhere on the board
/DR0: U13.43 (DATA16); also elsewhere on the board
/DR1: U13.42 (DATA17); also elsewhere on the board
/DR2: U13.41 (DATA18); also elsewhere on the board
/DR3: U13.40 (DATA19); also elsewhere on the board
/DR4: U13.39 (DATA20); also elsewhere on the board
/DR5: U13.38 (DATA21); also elsewhere on the board
/DR6: U13.37 (DATA22); also elsewhere on the board
/DR7: U13.36 (DATA23); also elsewhere on the board
/DVI_CLK: U13.57 (IDCK+); also elsewhere on the board
/DVI_DE: U13.2 (DE); also elsewhere on the board
/DVI_HS: U13.4 (HSYNC); also elsewhere on the board
/DVI_VS: U13.5 (VSYNC); also elsewhere on the board
/HDMI/HDMI5V: C88.1, J9.18 (+5V), U14.13 (5V_OUT)
/HDMI/HDMI_CT: R60.2, U14.12 (CT_HPD)
/HDMI/HDMI_HPD_B: J9.19 (HPD), U14.10 (HPD_B)
/HDMI/H_CEC: J9.13 (CEC), U14.7 (CEC_B)
/HDMI/H_SCL: J9.15 (SCL), U14.8 (SCL_B)
/HDMI/H_SDA: J9.16 (SDA), U14.9 (SDA_B)
/HDMI/TF_HI: R59.2, U13.3 (VREF), U13.9 (EDGE/HTPLG), U13.10 (~PD), U13.15 (BSEL/SCL)
/HDMI/TF_MSEN: R61.2, U13.11 (MSEN/PO1)
/HDMI/TF_TFADJ: R62.2, U13.19 (TFADJ)
/HDMI/TX0N: J9.9 (D0-), U13.24 (TX0-), U14.18 (D0-)
/HDMI/TX0P: J9.7 (D0+), U13.25 (TX0+), U14.17 (D0+)
/HDMI/TX1N: J9.6 (D1-), U13.27 (TX1-), U14.21 (D1-)
/HDMI/TX1P: J9.4 (D1+), U13.28 (TX1+), U14.20 (D1+)
/HDMI/TX2N: J9.3 (D2-), U13.30 (TX2-), U14.23 (D2-)
/HDMI/TX2P: J9.1 (D2+), U13.31 (TX2+), U14.22 (D2+)
/HDMI/TXCN: J9.12 (CK-), U13.21 (TXC-), U14.16 (CLK-)
/HDMI/TXCP: J9.10 (CK+), U13.22 (TXC+), U14.15 (CLK+)
/HDMI_HPD: U14.4 (HPD_A), U14.5 (LS_OE); also elsewhere on the board
GND: C79.2, C80.2, C81.2, C82.2, C83.2, C84.2, C85.2, C86.2, C87.2, C88.2, C89.2, C90.2, J9.2 (D2S), J9.5 (D1S), J9.8 (D0S), J9.11 (CKS), J9.17 (GND), J9.SH, U13.6 (CTL3/A3/DK3), U13.7 (CTL2/A2/DK2), U13.8 (CTL1/A1/DK1), U13.13 (ISEL/~RST), U13.14 (DSEL/SDA), U13.16 (DGND), U13.17 (PGND), U13.20 (TGND), U13.26 (TGND), U13.32 (TGND), U13.35 (DKEN), U13.48 (DGND), U13.56 (IDCK-), U13.64 (DGND), U13.65 (EP), U14.6 (GND), U14.14 (GND), U14.19 (GND); also elsewhere on the board

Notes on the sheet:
HDMI connector + TPD12S016 source-port companion (ESD, DDC/HPD/CEC level shift, 5 V current-limited switch)
TFP410 DVI/HDMI transmitter (pin-strapped: 24-bit, rising edge, no I2C)
